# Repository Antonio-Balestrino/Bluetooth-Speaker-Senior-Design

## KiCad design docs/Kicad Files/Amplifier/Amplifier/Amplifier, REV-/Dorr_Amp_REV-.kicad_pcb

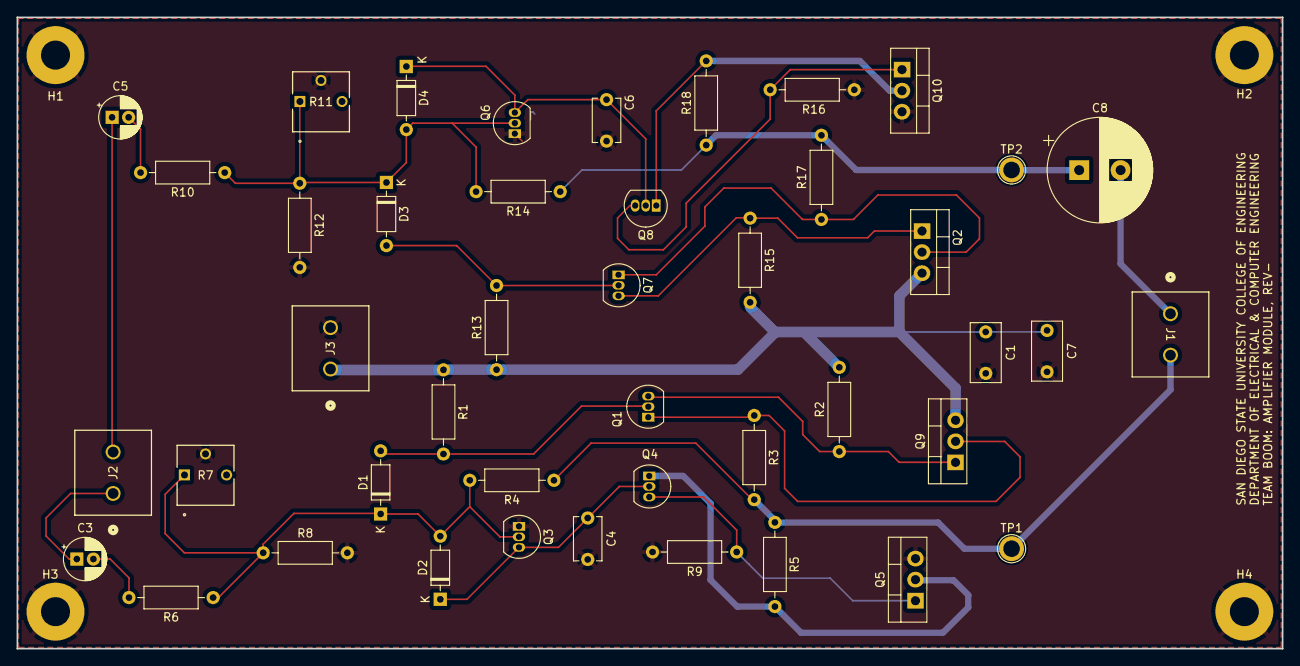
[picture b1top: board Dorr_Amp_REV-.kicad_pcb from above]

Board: 2 copper layers, 152.7 x 76.2 mm, 48 parts (0 on the bottom side), 23 nets.

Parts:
C1, C7: 0.22Uf; C_Rect_L7.0mm_W3.5mm_P5.00mm
C3, C5: 1Uf; CP_Radial_D5.0mm_P2.00mm
C4, C6: 1nF; C_Disc_D5.1mm_W3.2mm_P5.00mm
C8: 1000uF; CP_Radial_D12.5mm_P5.00mm
D1, D2, D3, D4: 1N4148; D_DO-35_SOD27_P7.62mm_Horizontal
H1, H2, H3, H4: MountingHole_Pad; MountingHole_3.5mm_Pad
J1: Speaker; CONN_1935776_PXC
J2: Input Terminals; CONN_1935776_PXC
J3: Power Input; CONN_1935776_PXC
Q1, Q3, Q6, Q7: 2N3904; TO-92_Inline
Q2, Q9: QD45H8G; TO-220-3_Vertical
Q4, Q8: 2N3906; TO-92_Inline
Q5, Q10: QD44H8G; TO-220-3_Vertical
R1, R6, R10, R13: 4.7k; R_Axial_DIN0207_L6.3mm_D2.5mm_P10.16mm_Horizontal
R2, R9, R15, R16: 10k; R_Axial_DIN0207_L6.3mm_D2.5mm_P10.16mm_Horizontal
R3, R5, R17, R18: 0.22; R_Axial_DIN0207_L6.3mm_D2.5mm_P10.16mm_Horizontal
R4, R14: 12k; R_Axial_DIN0207_L6.3mm_D2.5mm_P10.16mm_Horizontal
R7, R11: R_Variable; POT_3362P
R8, R12: 1.3k; R_Axial_DIN0207_L6.3mm_D2.5mm_P10.16mm_Horizontal
TP1, TP2: TestPoint; TestPoint_Plated_Hole_D2.0mm

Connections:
/18V: C1.1, C7.1, J3.1, Q2.3 (E), Q9.3 (E), R1.1, R2.2, R13.1, R15.2
GND: C1.2, C4.2, C6.2, C7.2, H1.1, H2.1, H3.1, H4.1, J3.2, Q3.1 (E), Q5.3 (E), Q6.1 (E), Q10.3 (E), R7.2, R8.2, R9.2, R11.2, R12.2, R16.2
unnamed: C3.2, R6.2
unnamed: C5.2, R10.2
unnamed: C8.1, R14.1, R17.2, R18.1, TP2.1
unnamed: D1.2 (A), Q1.2 (B), R1.2
unnamed: D1.1 (K), D2.2 (A), Q3.2 (B), R4.2, R6.1, R7.1, R8.1
unnamed: C4.1, D2.1 (K), Q3.3 (C), Q4.2 (B)
unnamed: D3.2 (A), Q7.2 (B), R13.2
unnamed: D3.1 (K), D4.2 (A), Q6.2 (B), R10.1, R11.1, R12.1, R14.2
unnamed: C6.1, D4.1 (K), Q6.3 (C), Q8.2 (B)
unnamed: C8.2, J1.1
unnamed: J1.2, R3.2, R4.1, R5.1, TP1.1
unnamed: C3.1, J2.1
unnamed: C5.1, J2.2
unnamed: Q1.3 (C), Q9.1 (B), R2.1
unnamed: Q1.1 (E), Q9.2 (C), R3.1
unnamed: Q2.1 (B), Q7.3 (C), R15.1
unnamed: Q2.2 (C), Q7.1 (E), R17.1
unnamed: Q4.3 (C), Q5.1 (B), R9.1
unnamed: Q4.1 (E), Q5.2 (C), R5.2
unnamed: Q8.3 (C), Q10.1 (B), R16.1
unnamed: Q8.1 (E), Q10.2 (C), R18.2

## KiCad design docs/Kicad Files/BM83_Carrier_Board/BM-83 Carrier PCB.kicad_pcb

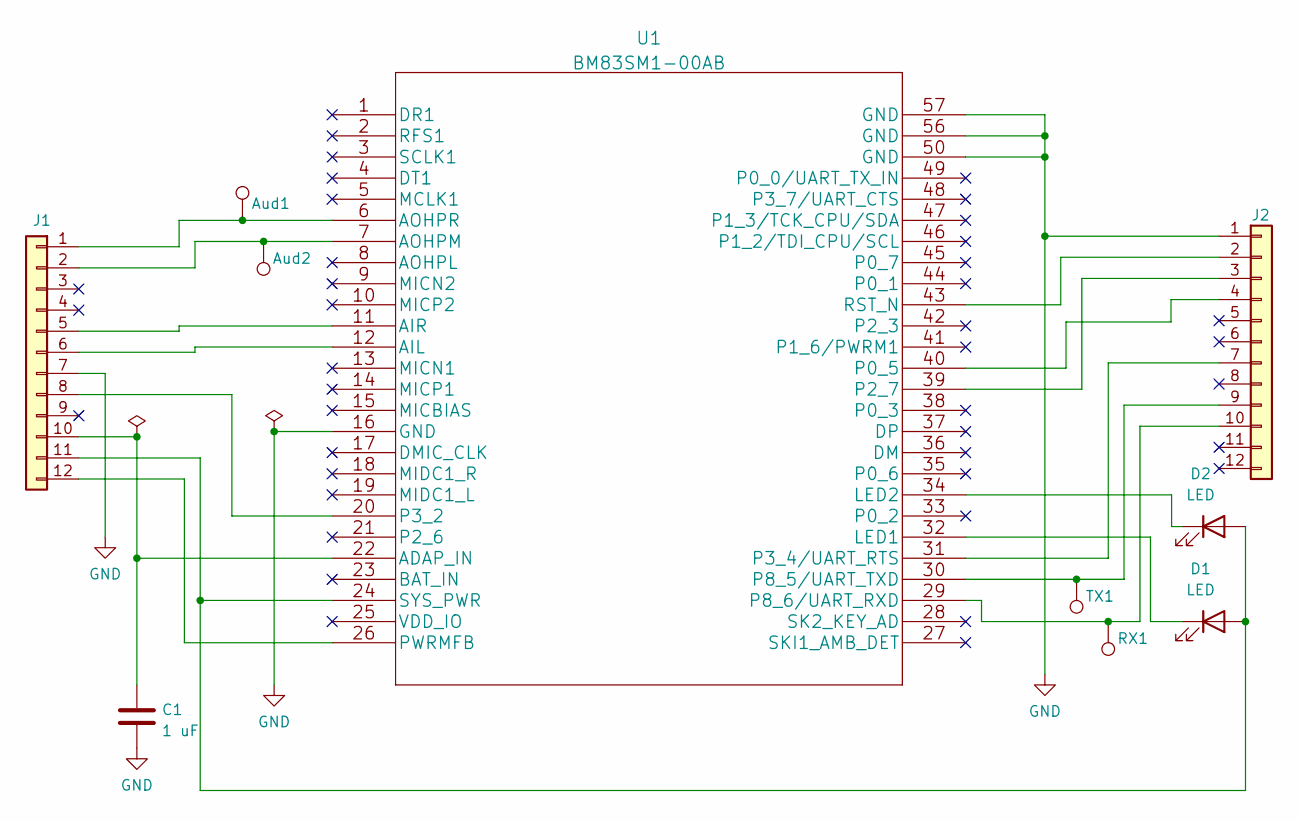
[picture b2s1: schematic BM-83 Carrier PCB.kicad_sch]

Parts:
Aud1, Aud2: TestPoint; TestPoint_THTPad_D1.0mm_Drill0.5mm
C1: 1 uF; C_Disc_D4.3mm_W1.9mm_P5.00mm
D1, D2: LED; LED_D3.0mm
J1, J2: Conn_01x12; PinHeader_1x12_P2.54mm_Vertical
RX1: TestPoint; TestPoint_THTPad_D1.0mm_Drill0.5mm
TX1: TestPoint; TestPoint_THTPad_D1.0mm_Drill0.5mm
U1: BM83SM1-00AB

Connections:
GND: C1.2, J1.7, J2.1, U1.16 (GND), U1.50 (GND), U1.56 (GND), U1.57 (GND)
unnamed: D1.2 (A), D2.2 (A), J1.11, U1.24 (SYS_PWR)
unnamed: D1.1 (K), U1.32 (LED1)
unnamed: D2.1 (K), U1.34 (LED2)
unnamed: Aud1.1, J1.1, U1.6 (AOHPR)
unnamed: Aud2.1, J1.2, U1.7 (AOHPM)
unnamed: J1.5, U1.11 (AIR)
unnamed: J1.6, U1.12 (AIL)
unnamed: J1.8, U1.20 (P3_2)
unnamed: C1.1, J1.10, U1.22 (ADAP_IN)
unnamed: J1.12, U1.26 (PWRMFB)
unnamed: J2.2, U1.43 (RST_N)
unnamed: J2.3, U1.39 (P2_7)
unnamed: J2.4, U1.40 (P0_5)
unnamed: J2.7, U1.31 (P3_4/UART_RTS)
unnamed: J2.9, TX1.1, U1.30 (P8_5/UART_TXD)
unnamed: J2.10, RX1.1, U1.29 (P8_6/UART_RXD)

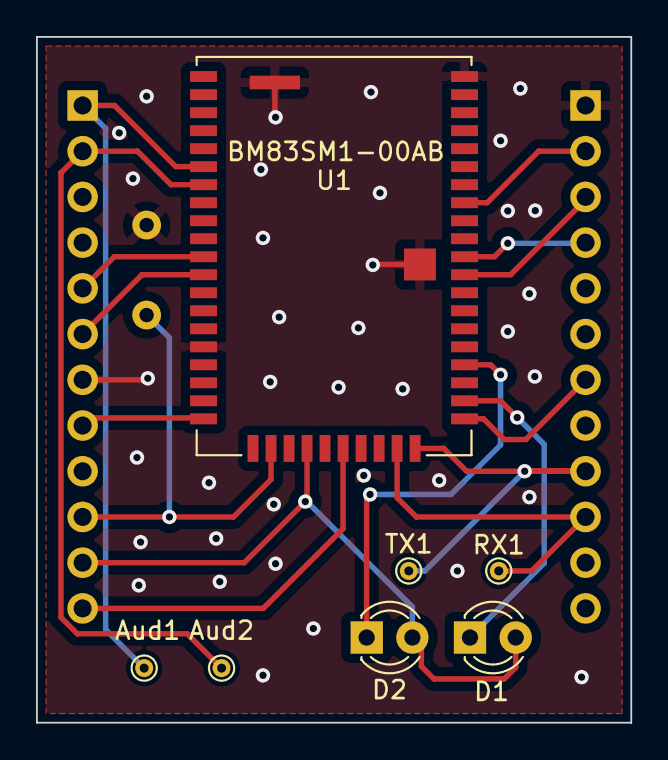
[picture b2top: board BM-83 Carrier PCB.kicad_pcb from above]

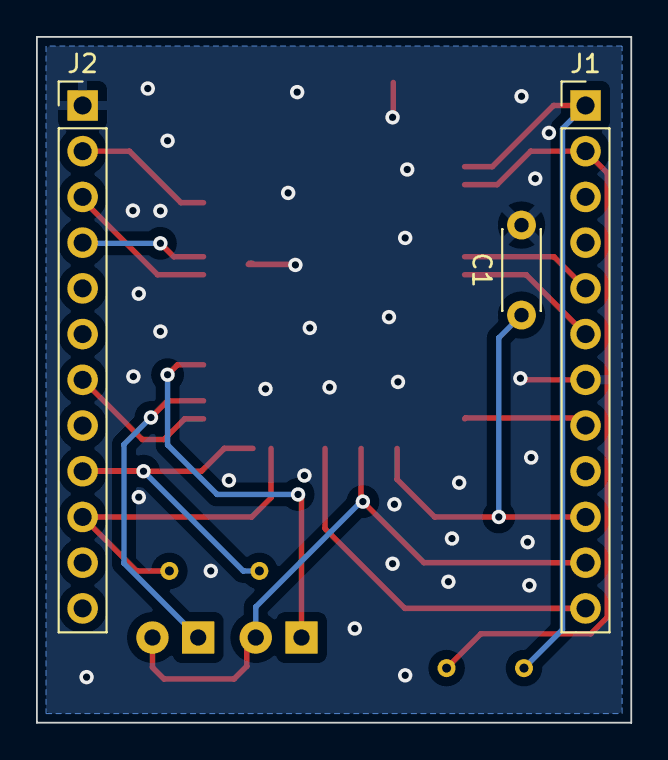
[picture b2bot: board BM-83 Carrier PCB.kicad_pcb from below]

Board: 2 copper layers, 33.0 x 38.1 mm, 10 parts (3 on the bottom side), 17 nets.

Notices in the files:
parts and their libraries:
Copyright 2021 Accelerated Designs. All rights reserved.
